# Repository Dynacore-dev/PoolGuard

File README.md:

# PoolGuard

PlatformIO/Arduino firmware for an ESP32 that controls a pool's filter pump plus two dosing pumps (pH, chlorine) on a schedule, exposes a small web dashboard, and reads water temperature from a DS18B20 sensor.

## Features

- **Scheduled pool pump** — up to 3 daily on/off time windows (`Config::POOL_INTERVALS`).
- **pH / chlorine dosing pumps** — start at a configured time and run for a configurable dose duration.
- **Safety interlock** — the pH/chlorine pumps only run in `AUTO`/`ON` mode while the pool pump's own output pin is driven HIGH. This is a GPIO read-back, not a real flow sensor or relay feedback signal, so it won't catch a relay/motor failure that leaves the pin driven HIGH.
- **pH/chlorine mutual exclusion** — the two dosing pumps can never run at the same time, in any mode combination (including both set to manual `ON`), since mixing the undiluted chemicals can be hazardous; pH takes priority and blocks chlorine while it's running. Toggle with `Config::CHEM_PUMP_INTERLOCK_ENABLED` (on by default).
- **Web dashboard** — self-contained HTML/CSS/JS page (no external assets) served directly from the ESP32, polling `/status` every second. Available in German or English (`Config::DASHBOARD_LANGUAGE`).
- **Manual override** — each device (pool, pH, chlorine) can be forced `OFF`/`ON` or left in `AUTO` (schedule-driven) via the dashboard.
- **Water temperature** — non-blocking DS18B20 readings, shown on the dashboard with a clear error state if the sensor is disconnected.
- **NTP time sync** — daily re-sync so schedules stay accurate without a RTC battery.
- **Optional dashboard auth** — HTTP Basic Auth for `/`, `/set`, and `/status`, off by default for use on a trusted home LAN. The server is plain HTTP (no TLS), so credentials travel unencrypted — only enable this on a network you trust.
- **OTA updates** — password-protected `ArduinoOTA`, enabled by default.
- **Watchdog** — reboots the device if the main loop ever hangs.

## Hardware

| Function          | Config constant   | Notes                          |
|--------------------|--------------------|---------------------------------|
| Temperature sensor  | `PIN_TEMP_SENSOR`  | DS18B20 via OneWire             |
| Pool filter pump    | `PIN_POOL_PUMP`    |                                  |
| pH dosing pump      | `PIN_PH_PUMP`      |                                  |
| Chlorine dosing pump| `PIN_CL_PUMP`      |                                  |

Pin numbers and all other hardware/environment specifics live in `src/Config.h` (see Setup below).

The KiCad PCB design this firmware runs on lives in [`hardware/PoolDosingController/`](hardware/PoolDosingController/README.md) — schematic, board layout, full BOM, and a self-contained project-local library (no third-party KiCad library packages needed to open it).

## Installation

Step-by-step guide to go from a fresh machine to a flashed board. All commands below are PlatformIO Core CLI (`pio`) — the same commands work whether you run them from a plain terminal or from inside an IDE's built-in terminal (VS Code + PlatformIO IDE extension, or CLion + the PlatformIO plugin both wrap the same CLI).

### 1. Install prerequisites

You need Python 3.9+, Git, and (for USB uploads) a driver for the board's USB-to-UART chip — usually Silicon Labs **CP210x** or WCH **CH340**, printed on the chip next to the USB port.

#### Windows

1. Install [Python 3](https://www.python.org/downloads/windows/) — during setup, check **"Add python.exe to PATH"**.
2. Install [Git for Windows](https://git-scm.com/download/win).
3. Install the USB driver for your board's chip: [CP210x driver](https://www.silabs.com/developer-tools/usb-to-uart-bridge-vcp-drivers) or [CH340 driver](https://www.wch-ic.com/downloads/CH341SER_EXE.html), whichever matches your board. Reboot afterwards if prompted.
4. Open PowerShell and install PlatformIO via [pipx](https://pipx.pypa.io/) (keeps it isolated from other Python tools):
   ```powershell
   py -m pip install --user pipx
   py -m pipx ensurepath
   ```
   Close and reopen PowerShell, then:
   ```powershell
   pipx install platformio
   ```
5. Verify: `pio --version`.
6. When you plug in the board, it should appear as a `COMx` port in Device Manager under "Ports (COM & LPT)".

#### macOS

1. Install [Homebrew](https://brew.sh/) if you don't already have it.
2. Install Python and pipx:
   ```sh
   brew install python pipx
   pipx ensurepath
   ```
   Restart your terminal, then:
   ```sh
   pipx install platformio
   ```
3. Git is already included with Xcode Command Line Tools (`xcode-select --install` if `git` isn't found).
4. Install the [CP210x VCP driver](https://www.silabs.com/developer-tools/usb-to-uart-bridge-vcp-drivers) if your board uses that chip (many newer macOS versions bundle CH340 support natively, but CP210x still needs the Silicon Labs driver). If macOS blocks the driver, allow it under **System Settings → Privacy & Security**.
5. Verify: `pio --version`. The board should show up as `/dev/tty.usbserial-*` or `/dev/tty.SLAB_USBtoUART`.

#### Linux (Debian/Ubuntu)

1. Install Python, pip, and Git:
   ```sh
   sudo apt update && sudo apt install -y python3 python3-pip python3-venv git
   ```
2. Install pipx and PlatformIO:
   ```sh
   python3 -m pip install --user pipx
   python3 -m pipx ensurepath
   ```
   Restart your terminal, then:
   ```sh
   pipx install platformio
   ```
3. Add your user to the `dialout` group so you can access `/dev/ttyUSB*` without `sudo`, then log out and back in (group changes need a new session):
   ```sh
   sudo usermod -aG dialout $USER
   ```
4. Verify: `pio --version`. The board should show up as `/dev/ttyUSB0` (or similar).
5. **Known conflict:** `ModemManager` (installed by default on many desktop distros) probes newly-plugged USB-serial devices and can corrupt the ESP32's serial output (garbled text in `pio device monitor`, or the port intermittently unusable) even though it never actually claims the device for a modem. If you hit this, tell it to permanently ignore this board's chip (adjust `idVendor`/`idProduct` if your board uses a different chip, e.g. CH340's `1a86`/`7523`):
   ```sh
   echo 'SUBSYSTEM=="tty", ATTRS{idVendor}=="10c4", ATTRS{idProduct}=="ea60", ENV{ID_MM_DEVICE_IGNORE}="1"' | sudo tee /etc/udev/rules.d/99-esp32-ignore-modemmanager.rules
   sudo udevadm control --reload-rules
   sudo udevadm trigger
   ```
   Unplug and replug the board afterwards.

### 2. Clone the repository

```sh
git clone https://github.com/Dynacore-dev/PoolGuard.git
cd PoolGuard
```

### 3. Configure secrets

Follow the **Setup** section below (`src/Config.h`) before building — `pio run` fails without it.

### 4. Build and flash via USB

Connect the ESP32 by USB, then from the project root:

```sh
pio run -t upload
```

PlatformIO auto-detects the port. If it picks the wrong one (e.g. multiple boards attached), pass it explicitly: `pio run -t upload --upload-port COM3` (Windows) or `--upload-port /dev/ttyUSB0` (macOS/Linux).

### 5. Watch the logs (optional)

```sh
pio device monitor
```

Close the monitor (Ctrl+C) before running another upload — the port can only be opened by one process at a time, and an open monitor will make `pio run -t upload` hang at "Connecting...".

### 6. Switch to OTA updates (optional)

Once the board has been flashed once via USB with `Config::OTA_ENABLED = true` and a real `Config::OTA_PASSWORD`, you can flash over WiFi instead of USB using the `esp32dev_ota` environment in `platformio.ini`. Set the same password as an environment variable (never commit it), then upload:

```sh
export OTA_PASSWORD=<same value as Config::OTA_PASSWORD>   # Windows PowerShell: $env:OTA_PASSWORD = "..."
pio run -e esp32dev_ota -t upload
```

This requires the board to already be powered on and connected to WiFi. `pio device monitor` does not work over OTA — it needs the USB serial connection.

## Setup

`src/Config.h` is gitignored (it holds real WiFi credentials, the dashboard password, and the OTA password) and must exist locally before building:

```sh
cp src/Config.example.h src/Config.h
```

Then edit `src/Config.h` and fill in at least:

- `Config::WIFI_SSID` / `Config::WIFI_PASSWORD`
- `Config::WEB_AUTH_USER` / `Config::WEB_AUTH_PASSWORD` (only used if `WEB_AUTH_ENABLED` is `true`)
- `Config::OTA_PASSWORD`

`pio run` will fail with `fatal error: Config.h: No such file or directory` if this file is missing. This is also where GPIO pin assignments, pump schedules (`POOL_INTERVALS`, `PH_START`, `CL_START`), dose durations, dashboard language, and timing/watchdog constants are configured.

## Commands

| Command | Purpose |
|---|---|
| `pio run` | Build the firmware |
| `pio run -t upload` | Upload to a connected board over USB |
| `pio run -e esp32dev_ota -t upload` | Upload over WiFi (OTA) — needs `OTA_PASSWORD` env var set; see Installation |
| `pio device monitor` | Serial monitor (115200 baud) |
| `pio run -t clean` | Clean build artifacts |

There is no test suite and no linter configured — `pio run` is the only correctness check available.

## Dependencies

The four Arduino libraries are vendored under `lib/` instead of being declared via `lib_deps`, so the project builds fully offline (no PlatformIO registry access needed, e.g. on a school laptop without internet):

- `OneWire`
- `DallasTemperature`
- `esp32async/AsyncTCP` and `esp32async/ESPAsyncWebServer` (maintained forks — not the original `me-no-dev` packages)

Since they're vendored, they never update on their own. See **Scripts** below for how to check for and pull newer versions.

## Scripts

| Script | Purpose |
|---|---|
| `scripts/update-libs.sh` | Re-downloads the four libraries from the PlatformIO registry and replaces `lib/`. Run occasionally on a machine with internet access, then review `git diff lib/` and rebuild before committing. |
| `scripts/check_lib_updates.py` | Runs automatically as a PlatformIO pre-build hook (`extra_scripts` in `platformio.ini`). Non-blocking, rate-limited (once/24h) check that prints a note if newer library versions are available — never fails or slows down an offline build. |
| `scripts/list-boards.sh [filter]` | Lists PlatformIO boards for Espressif and Arduino platforms (`espressif32`, `espressif8266`, `atmelavr`, `atmelsam`), optionally filtered by ID/name substring. Useful for finding the right `board = <ID>` value for `platformio.ini`. |

## Architecture

- **`Config.h`** — single source of truth for WiFi credentials, web server port, NTP/timezone settings, GPIO pin assignments, pump schedules, dosing durations, WiFi reconnect behavior, main loop delay, and the temperature sensor's polling interval.
- **`PoolGuard.ino`** — entry point. `setup()` arms the task watchdog and starts `ArduinoOTA` once WiFi is up; `loop()` resets the watchdog, reconnects WiFi if dropped, re-syncs time if needed, services OTA, and calls `ServerManager::handleLogic()`.
- **`ServerManager`** — the core controller. Holds three `Device` structs (pool, pH, chlorine) each with a pin, mode, and time windows; `handleLogic()` evaluates schedules and drives GPIO pins with the pump safety interlock and the pH/chlorine mutual exclusion; owns the `AsyncWebServer` and DS18B20 sensor; registers `GET /`, `POST /set?dev=<pool|ph|cl>&m=<0|1|2>`, and `GET /status`.
- **`WifiManager`** — STA-mode connection setup/retry.
- **`PoolTime` (`DailyTimeSync`)** — NTP time sync, re-synced periodically.
- **`DS18B20`** — non-blocking OneWire/DallasTemperature wrapper; `update()` must be polled regularly to refresh readings.

See `CLAUDE.md` for more implementation detail.

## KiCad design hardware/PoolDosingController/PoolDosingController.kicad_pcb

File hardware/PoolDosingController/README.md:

# PoolDosingController (KiCad hardware)

KiCad 10 PCB design for the ESP32 board that this repository's firmware runs on. It regulates power for the ESP32 and a DS18S20 temperature sensor, and switches four 12V output channels for pumps/relays.

## Overview

| | |
|---|---|
| MCU | ESP32-DevKitC (`U3`) |
| Board size | 108.9 x 78.0 mm, 2 layers |
| Power in | 12V via `J2` (2-pin screw terminal) |
| Regulated rails | +12V (unregulated, direct), +5V (`U1`, LM7805S linear regulator), +3.3V (from the ESP32-DevKitC's own onboard regulator) |
| Temperature sensor | DS18S20 (`U2`, onboard) + external sensor header `J1` (3-pin, +3.3V/DATA/GND) |
| Switched outputs | 4 channels via `J3` (8-pin screw terminal), each a low-side IRFZ44N MOSFET driven through an MMBT3904 transistor stage, with an SS16 flyback diode across the load |
| DRC status | 0 errors (see [Design status](#design-status)) |

## Output channels

`J3` provides 4 independent 12V low-side switched outputs (`D2`-`D5` / `Q1`-`Q12` / `R2`-`R13`, one MOSFET + driver transistor + flyback diode per channel):

1. Peristaltic dosing pump 1 (0.3-1A)
2. Peristaltic dosing pump 2 (0.3-1A)
3. Finder relay, drives the main pool filter pump (relay coil current only, ~30-70mA)
4. Reserve / spare channel

Each channel's copper (`D2-A`...`D5-A` nets) is on the `Pumpenausgaenge`→`PumpOutputs` netclass (1.5mm min. trace width, sized for the peristaltic pump's worst-case 1A draw with margin).

## Connectors

| Ref | Type | Function |
|---|---|---|
| `J1` | 3-pin, 2.54mm (Xinya XY308) | External DS18S20 sensor: +3.3V / DATA / GND |
| `J2` | 2-pin, 5.0mm (Phoenix) | +12V power input |
| `J3` | 8-pin, 5.0mm (Phoenix) | 4x switched 12V output channels (2 pins each) |

## Netclasses

| Name | Nets | Trace width | Via (dia/drill) |
|---|---|---|---|
| `PumpOutputs` | `Net-(D2-A)` … `Net-(D5-A)` | 1.5mm | 1.0 / 0.5mm |
| `Supply_12V` | `+12V`, `GND` | 1.0mm | 1.0 / 0.5mm |
| `Supply_Logic` | `+5V`, `+3.3V` | 0.6mm | 0.6 / 0.3mm |
| `Default` | everything else (control/signal lines) | 0.2mm | 0.6 / 0.3mm |

`+12V` and `GND` are additionally backed by copper pours (zones) on `B.Cu`/`F.Cu`, so the netclass trace width only governs short stub connections into the pour, not the bulk current path.

## Bill of materials

Full BOM: [`PoolDosingController-BOM.csv`](PoolDosingController-BOM.csv). Summary:

| Ref | Qty | Value | MPN |
|---|---|---|---|
| C1 | 1 | 0.33uF | |
| C2, C3 | 2 | 0.1uF | |
| C4, C5, C6 | 3 | 10uF | |
| D1 | 1 | 1N4001 | |
| D2, D3, D4, D5 | 4 | SS16 | |
| J1 | 1 | 3-pin 2.54mm terminal block | |
| J2 | 1 | 2-pin 5.0mm terminal block | |
| J3 | 1 | 8-pin 5.0mm terminal block | |
| Q1-Q8 | 8 | MMBT3904 | |
| Q9-Q12 | 4 | IRFZ44N | |
| R1 | 1 | 2.2K | |
| R2, R3, R4, R5 | 4 | 220 | |
| R6-R13 | 8 | 10K | |
| U1 | 1 | LM7805S | L7805ABD2T-TR |
| U2 | 1 | DS18S20 | DS18S20+ |
| U3 | 1 | ESP32-DevKitC | ESP32-DEVKITC-32E |

C2's footprint (`PCM_Capacitor_SMD_AKL:C_0805_2012Metric`) has a documented, not-yet-installed alternate part on its `LCSC_Alt_0402` field: JLCPCB C1525 (Samsung CL05B104KO5NNNC, 0402, 100nF 16V X7R, Basic). Its footprint (`CAPC2012X140N`) is included under `library/footprints/` if you want to switch to it.

## Design status

Last full design review: **0 DRC errors**. Remaining warnings (non-blocking):
- 199x `connection_width` — thermal spoke connections to the copper pours, expected/cosmetic.
- 32x `text_height` — a few silkscreen labels below the strict 0.8mm rule.
- 4x `lib_footprint_mismatch` — the embedded footprint copies for `J1`/`J2`/`J3`/`C1` have drifted slightly from the current version of their (stock KiCad) libraries; purely a library-vs-board diff, not a design error.
- 3x info: `+12V`/`+5V`/`+3.3V` have no test point (informational only).

## Opening this project

This folder is fully self-contained: `library/` holds local copies of every non-stock symbol library, footprint library, and 3D model this design uses (`sym-lib-table`/`fp-lib-table` point at them via `${KIPRJMOD}`), so `git clone` + open in KiCad 10 works without installing any third-party library packages first. The only gap is a missing 3D model for `J1`'s exact connector (cosmetic 3D-preview only, a similarly-sized substitute is used); see the netclass/library setup notes in the project's commit history for details.

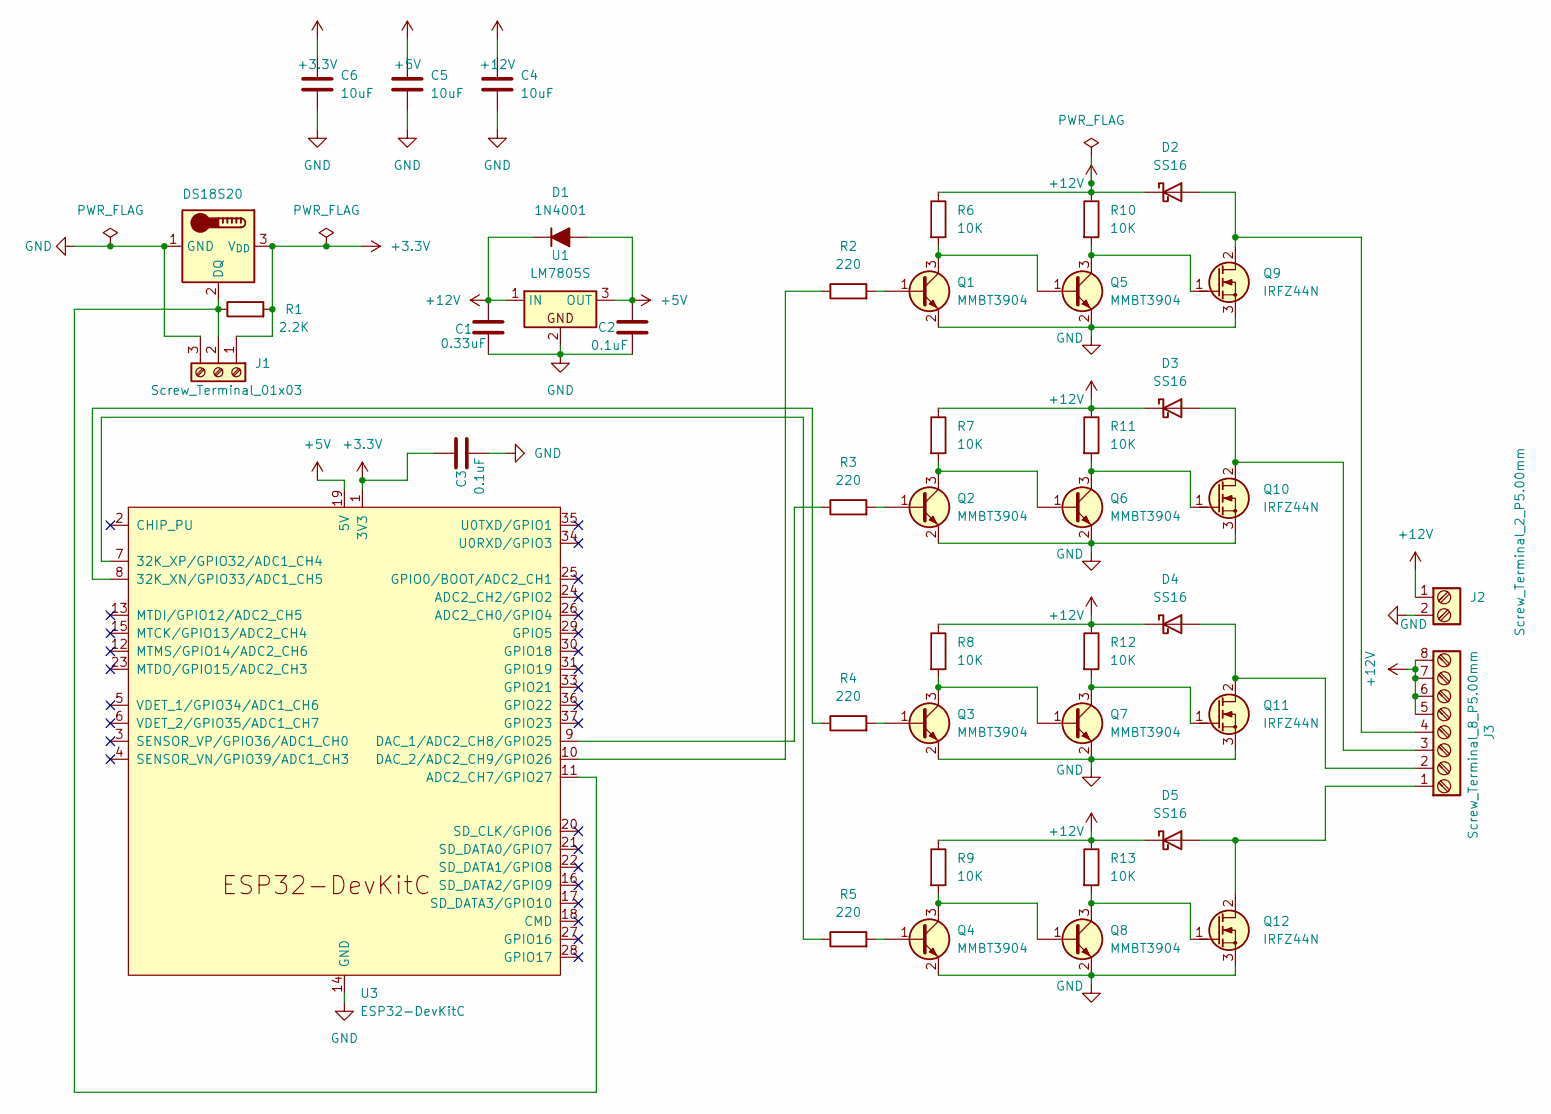
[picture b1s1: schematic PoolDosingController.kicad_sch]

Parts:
C1: 0.33uF; C_1206_3216Metric_Pad1.33x1.80mm_HandSolder
C2, C3: 0.1uF; C_0805_2012Metric; LCSC_Alt_0402 C1525 (Samsung CL05B104KO5NNNC, 0402, 1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
C4, C5, C6: 10uF; C_1206_3216Metric_Pad1.33x1.80mm_HandSolder
D1: 1N4001; D_DO-41_SOD81_P7.62mm_Horizontal
D2, D3, D4, D5: SS16; D_SMA
J1: Screw_Terminal_01x03; TerminalBlock_Xinya_XY308-2.54-3P_1x03_P2.54mm_Horizontal
J2: Screw_Terminal_2_P5.00mm; TerminalBlock_Phoenix_PT-1,5-2-5.0-H_1x02_P5.00mm_Horizontal
J3: Screw_Terminal_8_P5.00mm; TerminalBlock_Phoenix_PT-1,5-8-5.0-H_1x08_P5.00mm_Horizontal
Q1, Q2, Q3, Q4, Q5, Q6, Q7, Q8: MMBT3904; SOT-23
Q9, Q10, Q11, Q12: IRFZ44N; TO-220-3_Vertical_GDS
R1: 2.2K; R_1206_3216Metric_Pad1.42x1.75mm_HandSolder
R2, R3, R4, R5: 220; R_1206_3216Metric_Pad1.42x1.75mm_HandSolder
R6, R7, R8, R9, R10, R11, R12, R13: 10K; R_1206_3216Metric_Pad1.42x1.75mm_HandSolder
U1: LM7805S; TO-263-3_TabPin2; MPN L7805ABD2T-TR
U2: DS18S20; TO-92_Inline; MPN DS18S20+
U3: ESP32-DevKitC; MPN ESP32-DEVKITC-32E

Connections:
+3.3V: C3.1, C6.1, J1.1, R1.2, U2.3 (V_{DD}), U3.1 (3V3)
+5V: C2.1, C5.1, D1.2 (A), U1.3 (OUT), U3.19 (5V)
+12V: C1.1, C4.1, D1.1 (K), D2.1 (K), D3.1 (K), D4.1 (K), D5.1 (K), J2.1, J3.5, J3.6, J3.7, J3.8, R6.1, R7.1, R8.1, R9.1, R10.1, R11.1, R12.1, R13.1, U1.1 (IN)
GND: C1.2, C2.2, C3.2, C4.2, C5.2, C6.2, J1.3, J2.2, Q1.2 (E), Q2.2 (E), Q3.2 (E), Q4.2 (E), Q5.2 (E), Q6.2 (E), Q7.2 (E), Q8.2 (E), Q9.3 (S), Q10.3 (S), Q11.3 (S), Q12.3 (S), U1.2, U2.1 (GND), U3.14 (GND), U3.32 (GND), U3.38 (GND)
unnamed: D2.2 (A), J3.4, Q9.2 (D)
unnamed: D3.2 (A), J3.3, Q10.2 (D)
unnamed: D4.2 (A), J3.2, Q11.2 (D)
unnamed: D5.2 (A), J3.1, Q12.2 (D)
unnamed: J1.2, R1.1, U2.2 (DQ), U3.11 (ADC2_CH7/GPIO27)
unnamed: Q1.1 (B), R2.2
unnamed: Q1.3 (C), Q5.1 (B), R6.2
unnamed: Q2.1 (B), R3.2
unnamed: Q2.3 (C), Q6.1 (B), R7.2
unnamed: Q3.1 (B), R4.2
unnamed: Q3.3 (C), Q7.1 (B), R8.2
unnamed: Q4.1 (B), R5.2
unnamed: Q4.3 (C), Q8.1 (B), R9.2
unnamed: Q5.3 (C), Q9.1 (G), R10.2
unnamed: Q6.3 (C), Q10.1 (G), R11.2
unnamed: Q7.3 (C), Q11.1 (G), R12.2
unnamed: Q8.3 (C), Q12.1 (G), R13.2
unnamed: R4.1, U3.8 (32K_XN/GPIO33/ADC1_CH5)
unnamed: R5.1, U3.7 (32K_XP/GPIO32/ADC1_CH4)
unnamed: R3.1, U3.9 (DAC_1/ADC2_CH8/GPIO25)
unnamed: R2.1, U3.10 (DAC_2/ADC2_CH9/GPIO26)

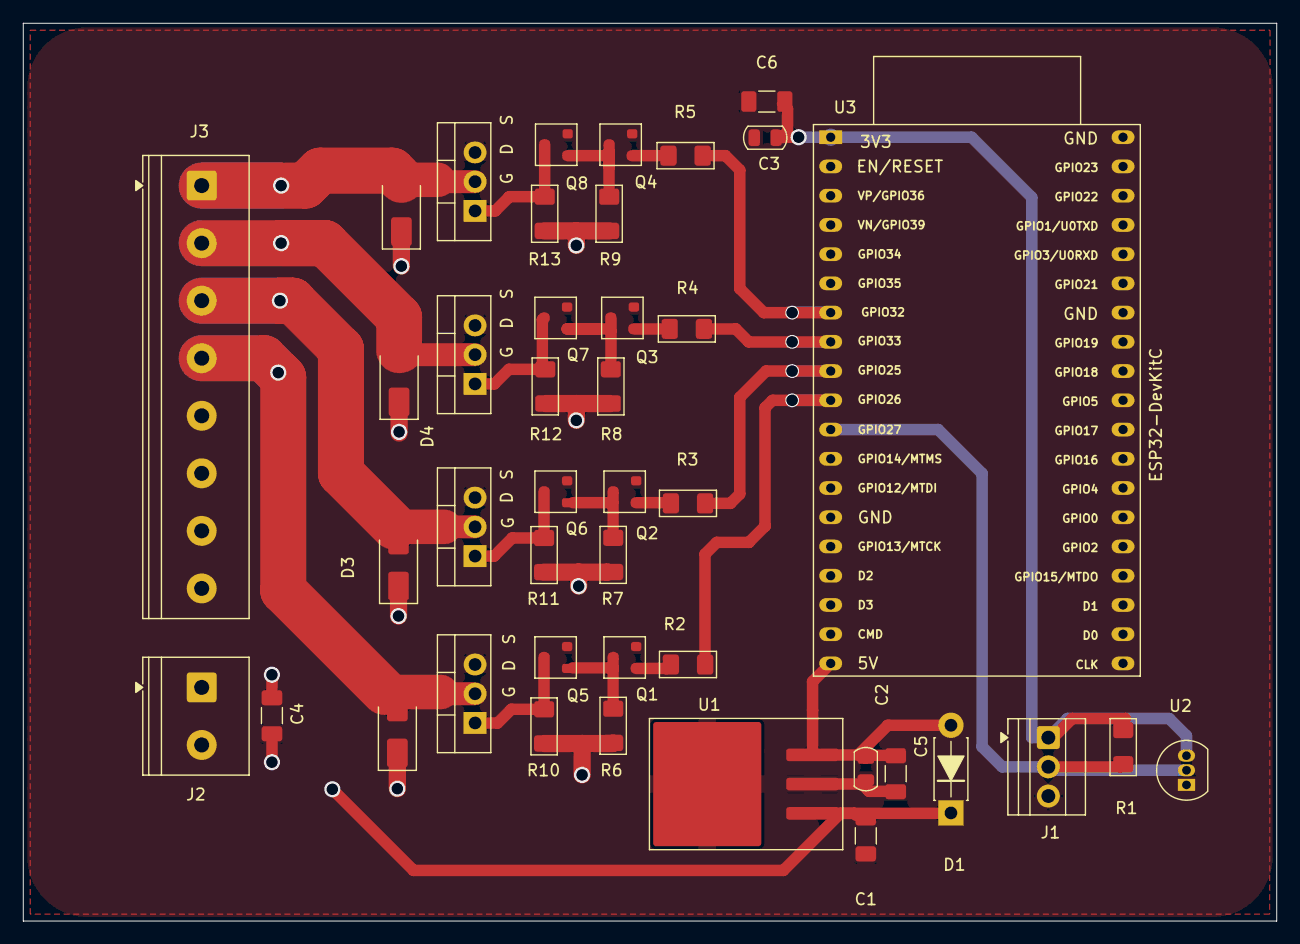
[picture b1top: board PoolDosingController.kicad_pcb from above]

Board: 2 copper layers, 108.9 x 78.0 mm, 42 parts (0 on the bottom side), 25 nets.

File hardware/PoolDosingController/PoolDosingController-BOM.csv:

"#","References","Qty","Value","Footprint","MPN","DNP"
"1","C1","1","0.33uF","Capacitor_SMD:C_1206_3216Metric_Pad1.33x1.80mm_HandSolder","",""
"2","C2, C3","2","0.1uF","PCM_Capacitor_SMD_AKL:C_0805_2012Metric","",""
"3","C4, C5, C6","3","10uF","Capacitor_SMD:C_1206_3216Metric_Pad1.33x1.80mm_HandSolder","",""
"4","D1","1","1N4001","PCM_Diode_THT_AKL:D_DO-41_SOD81_P7.62mm_Horizontal","",""
"5","D2, D3, D4, D5","4","SS16","Diode_SMD:D_SMA","",""
"6","J1","1","Screw_Terminal_01x03","TerminalBlock:TerminalBlock_Xinya_XY308-2.54-3P_1x03_P2.54mm_Horizontal","",""
"7","J2","1","Screw_Terminal_2_P5.00mm","TerminalBlock_Phoenix:TerminalBlock_Phoenix_PT-1,5-2-5.0-H_1x02_P5.00mm_Horizontal","",""
"8","J3","1","Screw_Terminal_4_P5.00mm","TerminalBlock_Phoenix:TerminalBlock_Phoenix_PT-1,5-8-5.0-H_1x08_P5.00mm_Horizontal","",""
"9","Q1, Q2, Q3, Q4, Q5, Q6, Q7, Q8","8","MMBT3904","PCM_Package_TO_SOT_SMD_AKL:SOT-23","",""
"10","Q9, Q10, Q11, Q12","4","IRFZ44N","PCM_Package_TO_SOT_THT_AKL:TO-220-3_Vertical_GDS","",""
"11","R1","1","2.2K","PCM_Resistor_SMD_AKL:R_1206_3216Metric_Pad1.42x1.75mm_HandSolder","",""
"12","R2, R3, R4, R5","4","220","PCM_Resistor_SMD_AKL:R_1206_3216Metric_Pad1.42x1.75mm_HandSolder","",""
"13","R6, R7, R8, R9, R10, R11, R12, R13","8","10K","PCM_Resistor_SMD_AKL:R_1206_3216Metric_Pad1.42x1.75mm_HandSolder","",""
"14","U1","1","LM7805S","PCM_Package_TO_SOT_SMD_AKL:TO-263-3_TabPin2","L7805ABD2T-TR",""
"15","U2","1","DS18S20","Package_TO_SOT_THT:TO-92_Inline","DS18S20+",""
"16","U3","1","ESP32-DevKitC","PCM_Espressif:ESP32-DevKitC","ESP32-DEVKITC-32E",""
